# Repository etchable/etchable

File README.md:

<h1 align="center">etchable</h1>

<p align="center">
  A friendly little tool for designing circuit boards.<br />
  Sketch your idea, route your traces, etch what matters.
</p>

<p align="center">
  <a href="https://etchable.net">etchable.net</a> ·
  <a href="https://github.com/etchable/etchable/releases">Releases</a> ·
  <a href="docs/development.md">For developers</a>
</p>

---

Describe the board you want and etchable draws you a schematic. Move parts
around, wire pin to pin, and name your power rails right on the canvas — or
ask for a change in chat and watch the drawing follow. Everything you make is
saved as ordinary files on your Mac, so your work stays yours.

- **Start from a sentence.** "A 3.3 V supply with a status LED" is enough to
  get a first schematic on the canvas, ready for you to look over.
- **Draw it yourself.** Place parts from the library, drag them onto the grid,
  wire pin to pin, label ground and power. Undo and redo like any editor.
- **Or just ask.** Click the parts you mean and they become the subject of your
  next message — "make this divider 10k" needs no names or numbers.
- **Real parts you can buy.** Search JLCPCB from the parts panel and see stock,
  price, and whether it's a basic part. Pick one and its symbol and footprint
  come with it.
- **Always live.** Change a file outside the app and the canvas redraws;
  mistakes collect in a Problems panel instead of failing quietly.

## Install

With [Homebrew](https://brew.sh):

```sh
brew install --cask etchable/etchable/etchable
```

Or download the `.dmg` from the [latest release](https://github.com/etchable/etchable/releases/latest).

You'll need:

- A Mac with Apple Silicon, running macOS 13 or newer
- [Claude Code](https://claude.com/claude-code) installed and signed in —
  etchable works through it on your behalf

## Your first board

1. Open etchable and describe the board you want on the welcome screen — or
   open a project you already have.
2. The first build of a board fetches its parts libraries into
   `~/.etchable/cache`. Later builds are fast.
3. Click a part, ask for what you want in the chat, approve the change, and
   watch the canvas update.

A small demo project ships in this repo at `examples/demo` — open that one to
poke around without starting from scratch.

## Early days

etchable is young and moving fast. Wires are drawn between nearby parts while
power and ground use labels at each pin (the usual schematic shorthand);
multi-board projects aren't there yet, and turning a finished schematic into a
physical board layout is still ahead. The rough edges are listed honestly in
[status and limits](docs/development.md#status-vs-plan). Found something
broken? [Open an issue](https://github.com/etchable/etchable/issues).

## License

[MIT](LICENSE)

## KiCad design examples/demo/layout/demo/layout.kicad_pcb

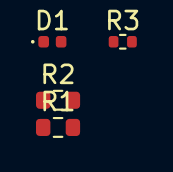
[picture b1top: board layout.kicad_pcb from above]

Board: 2 copper layers, 4 parts (0 on the bottom side), 4 nets, no tracks yet.

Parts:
D1: VLMS1500-GS08; LED_0402_1005Metric
R1: ERJ-3EKF1003V; R_0603_1608Metric
R2: ERJ-3EKF4702V; R_0603_1608Metric
R3: ERJ-2RKF1001X; R_0402_1005Metric

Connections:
GND: D1.1, R2.2
LED_A: D1.2, R3.2
VCC_3V3: R1.1, R3.1
V_SENSE: R1.2, R2.1
